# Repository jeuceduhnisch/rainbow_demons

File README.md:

# Rainbow Demons

Rainbow Demons is an independently designed Daisy Patch SM Eurorack
buffer-manipulation instrument.

## Releases

- The repository root preserves the original tested working build from
  2026-08-11, including its firmware, documentation and fabrication files.
- `Rainbow_Demons_v2/` contains the corrected 18HP hardware revision.
- `Rainbow_Demons_v2/release/` contains firmware and documentation v2.0.1.
- `Rainbow_Demons_v2/Rainbow_Demons_v2.0.1.zip` is the current complete release.
- `Rainbow_Demons_v2/Rainbow_Demons_v2.0.0.zip` remains the immutable rollback
  package.

## Version 2.0.1

Version 2 adds:

- Clock-toggle recording in Slice and Scatter: start, stop/play, start fresh.
- A Mode 2 Feedback density control that creates increasingly frequent and
  shorter randomized recording windows clockwise.
- Physical Record and REC CV priority over Mode 2 automation.
- Automatic four-second Slice and eight-second Scatter capture limits.
- A hardware-tested audio block-size correction that moves the callback cadence
  from an audible 3 kHz to 24 kHz and removes the high-pitched harmonic comb.

The v2.0.1 firmware was built, flashed, and tested on the target module on
2026-09-29. Tape, Slice, Scatter, recording, playback, three-head operation,
controls and mode switching passed without reported crackling or dropouts.

## Independent-design disclaimer

Rainbow Demons is inspired by broad buffer-manipulation ideas associated with
MTL ASM's Count to 5. It is not a clone, reproduction, port, or claim of exact
pedal behavior. No original source code, firmware, schematics, PCB files, or
proprietary design material were used. This project is not affiliated with or
endorsed by MTL ASM.

## License

This project is released under the Unlicense. See [LICENSE](LICENSE).

## Acknowledgments

Documentation, cleanup, and release organization were assisted by OpenAI Codex.

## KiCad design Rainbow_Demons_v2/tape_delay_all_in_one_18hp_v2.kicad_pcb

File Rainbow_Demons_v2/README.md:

# Rainbow Demons v2

## Tape Delay 18HP All-In-One PCB and Faceplate

This revision corrects the Alpha RD901F potentiometer and QingPu WQP-PJ398SM / Thonkiconn footprints, fixes the rear-mounted Daisy Patch SM pin mirroring, and removes the carrier PCB material behind the top and bottom Eurorack rails. The separate faceplate remains the full 128.5 mm Eurorack height.

Electrical notes:

- 10-pin Eurorack power is routed as pins 1-2 `-12V`, pins 3-8 `GND`, pins 9-10 `+12V`.
- The Patch SM `3V3` output on A10 feeds the five potentiometer high-side pins.
- The Patch SM `5V` output is not used by this tape-delay control board.
- Potentiometers are wired as `GND / wiper signal / 3V3`.
- Pot electrical pads are on 2.50 mm centers and mounting tabs are 9.60 mm apart, matching KiCad's official Alpha RD901F-40-00D footprint.
- RV2 is rotated 180 degrees behind the panel so its real Alpha-style pin row clears the Daisy Patch SM A5/A6 area.
- FREEZE and REVERSE are momentary switches to ground using the Wurth `430476085716` 12 x 12 mm THT footprint.
- Each LED has two LED holes plus two inline series-resistor holes; install a resistor between `R_SIG` and `R_LED_A`.
- The square/rectangular LED hole is cathode/ground.
- The square/rectangular jack hole is sleeve/ground.
- Jack pad centers are sleeve `-6.48 mm`, switch normal `-3.38 mm`, and tip `+4.92 mm` relative to the panel jack center.
- Each jack includes the manufacturer-recommended 3.0 mm NPTH beneath the barrel center.
- The populated carrier outline is 91.44 x 111.50 mm, spanning panel coordinates y=8.50 through y=120.00; there is no carrier material in either rail zone.
- The rear-mounted Patch SM footprint is mirrored before rotation so carrier A1 lands on module A1, A5 on A5, and all other named pins remain one-to-one.
- IN R is normalled from IN L through the jack switch contact.
- IN R is normalled from IN L. The OUT L and OUT R switch contacts are intentionally unconnected.

Fabrication status:

- The main PCB and faceplate were generated as KiCad 10 PCB files.
- KiCad CLI DRC on 2026-07-21 reported 0 violations and 0 unconnected items for both generated boards.
- Run KiCad DRC again before ordering after any manual edits.
- This layout uses generic 9 mm vertical pot, QingPu/Thonkiconn PJ398SM-style 3-pin jack, and 5 mm LED footprints. Verify against the exact parts you will buy before a full production order.

Files:

- `tape_delay_all_in_one_18hp_v2.kicad_pcb`: routed main PCB with corrected footprints, power mapping, and rail clearance.
- `tape_delay_faceplate_18hp_v2.kicad_pcb`: matching full-height FR4 faceplate.
- `faceplate_editable.svg`: editable faceplate art/text template.
- `tape_delay_all_in_one_wiring_map.csv`: Patch SM pin assignments.
- `main_gerbers.zip`: main PCB fabrication package, after export.
- `faceplate_gerbers.zip`: faceplate fabrication package, after export.

## Firmware and build release 2.0.1

The complete clock-toggle and random-density firmware release is in
`release/`. It includes source, flashable binary, BOM, build guide, PCB
modifications, quick start and the six-page combined manual.

The packaged current release is `Rainbow_Demons_v2.0.1.zip`; the unchanged
`Rainbow_Demons_v2.0.0.zip` is retained for rollback. Version 2 adds clock-edge
start/stop recording in Slice and Scatter plus randomized Mode 2 recording
density on the Feedback control. Version 2.0.1 changes only the audio block
size from 16 to 2, moving the callback cadence from 3 kHz to 24 kHz. The new
firmware built, flashed and passed the complete hands-on mode test on
2026-09-29 without reported crackling or dropouts.

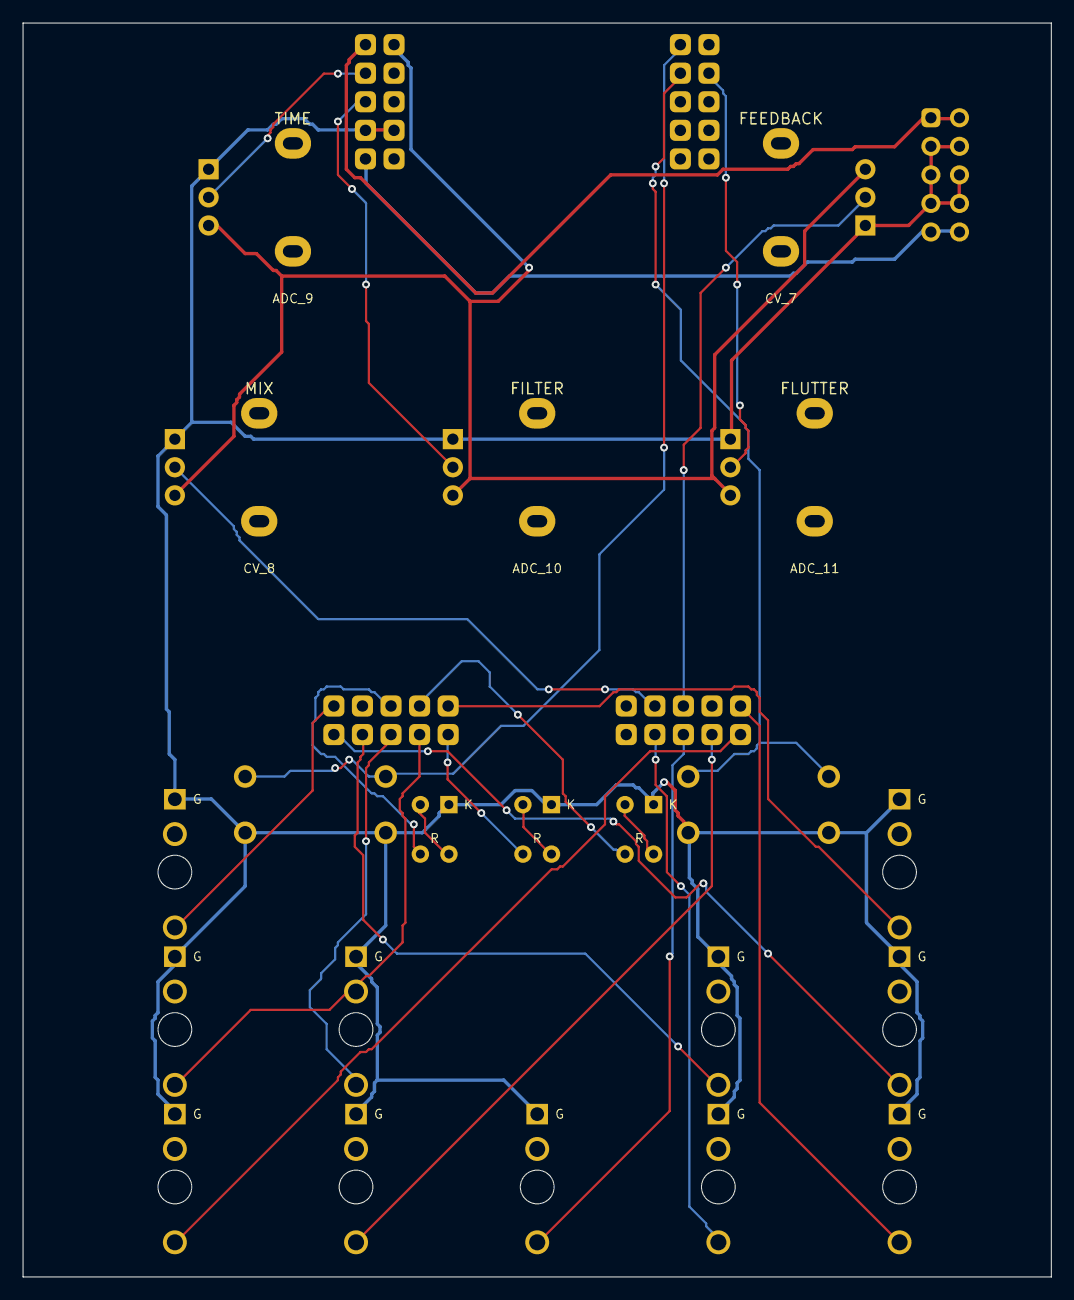
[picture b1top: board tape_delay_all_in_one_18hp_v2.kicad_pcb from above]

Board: 2 copper layers, 91.4 x 111.5 mm, 34 parts (0 on the bottom side), 28 nets.

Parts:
D1: TEMPO; LED_5mm_With_Series_Resistor_Pads
D2: FREEZE; LED_5mm_With_Series_Resistor_Pads
D3: REV; LED_5mm_With_Series_Resistor_Pads
J1: CLK IN; Jack_3.5mm_QingPu_WQP-PJ398SM_ShaftOrigin
J1_BARREL, J2_BARREL, J3_BARREL, J4_BARREL, J5_BARREL, J6_BARREL, J7_BARREL, J8_BARREL, J9_BARREL, J10_BARREL, J11_BARREL: NPTH 3mm; NPTH_3mm
J2: CLK OUT; Jack_3.5mm_QingPu_WQP-PJ398SM_ShaftOrigin
J3: IN L; Jack_3.5mm_QingPu_WQP-PJ398SM_ShaftOrigin
J4: IN R; Jack_3.5mm_QingPu_WQP-PJ398SM_ShaftOrigin
J5: OUT L; Jack_3.5mm_QingPu_WQP-PJ398SM_ShaftOrigin
J6: OUT R; Jack_3.5mm_QingPu_WQP-PJ398SM_ShaftOrigin
J7: TIME; Jack_3.5mm_QingPu_WQP-PJ398SM_ShaftOrigin
J8: FEEDBACK; Jack_3.5mm_QingPu_WQP-PJ398SM_ShaftOrigin
J9: MIX; Jack_3.5mm_QingPu_WQP-PJ398SM_ShaftOrigin
J10: FILTER; Jack_3.5mm_QingPu_WQP-PJ398SM_ShaftOrigin
J11: FLUTTER; Jack_3.5mm_QingPu_WQP-PJ398SM_ShaftOrigin
J_PWR: 10 pin Eurorack power; EURORACK_10PIN_POWER_REAR
M1: Daisy Patch SM; Daisy_Patch_SM_PTH_Rear
RV1: TIME; Alpha_RD901F_9mm_Vertical_Pot_ShaftOrigin
RV2: FEEDBACK; Alpha_RD901F_9mm_Vertical_Pot_ShaftOrigin
RV3: MIX; Alpha_RD901F_9mm_Vertical_Pot_ShaftOrigin
RV4: FILTER; Alpha_RD901F_9mm_Vertical_Pot_ShaftOrigin
RV5: FLUTTER; Alpha_RD901F_9mm_Vertical_Pot_ShaftOrigin
SW1, SW2: Wurth 430476085716; Wurth_WS-TATV_430476085716_12x12_THT

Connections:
ADC_9: M1.A2, RV1.2_SIG
ADC_10: M1.A3, RV4.2_SIG
ADC_11: M1.D9, RV5.2_SIG
AUDIO_IN_LEFT: J3.TIP_SIG, J4.SW, M1.B4
AUDIO_IN_RIGHT: J4.TIP_SIG, M1.B3
AUDIO_OUT_LEFT: J5.TIP_SIG, M1.B2
AUDIO_OUT_RIGHT: J6.TIP_SIG, M1.B1
CV_1: J7.TIP_SIG, M1.C5
CV_2: J8.TIP_SIG, M1.C4
CV_3: J9.TIP_SIG, M1.C3
CV_4: J10.TIP_SIG, M1.C2
CV_5: J11.TIP_SIG, M1.C6
CV_7: M1.C8, RV2.2_SIG
CV_8: M1.C9, RV3.2_SIG
FREEZE_BTN: M1.D1, SW1.1_SIG, SW1.2_SIG
GATE_IN_1: J1.TIP_SIG, M1.B10
GATE_OUT_2: J2.TIP_SIG, M1.B6
GND: D1.K_GND, D2.K_GND, D3.K_GND, J1.SLEEVE_GND, J2.SLEEVE_GND, J3.SLEEVE_GND, J4.SLEEVE_GND, J5.SLEEVE_GND, J6.SLEEVE_GND, J7.SLEEVE_GND, J8.SLEEVE_GND, J9.SLEEVE_GND, J10.SLEEVE_GND, J11.SLEEVE_GND, J_PWR.3, J_PWR.4, J_PWR.5, J_PWR.6, J_PWR.7, J_PWR.8, M1.A4, M1.A7, RV1.1_GND, RV2.1_GND, RV3.1_GND, RV4.1_GND, RV5.1_GND, SW1.3_GND, SW1.4_GND, SW2.3_GND, SW2.4_GND
LED_FREEZE: D2.R_SIG, M1.B5
LED_FREEZE_A: D2.A, D2.R_LED_A
LED_REVERSE: D3.R_SIG, M1.B7
LED_REVERSE_A: D3.A, D3.R_LED_A
LED_TEMPO: D1.R_SIG, M1.B8
LED_TEMPO_A: D1.A, D1.R_LED_A
PWR_3V3: M1.A10, RV1.3_3V3, RV2.3_3V3, RV3.3_3V3, RV4.3_3V3, RV5.3_3V3
PWR_+12V: J_PWR.9, J_PWR.10, M1.A5
PWR_-12V: J_PWR.1, J_PWR.2, M1.A1
REVERSE_BTN: M1.D2, SW2.1_SIG, SW2.2_SIG

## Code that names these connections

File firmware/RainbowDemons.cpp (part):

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    // Preserve the already-built carrier wiring exactly:
    // TIME/ADC_9, FILTER/ADC_10, FLUTTER/ADC_11,
    // FEEDBACK/CV_7 and MIX/CV_8. The five panel CV inputs remain CV_1..CV_5.
    const float time_p = Clamp(patch.GetAdcValue(ADC_9), 0.0f, 1.0f);
    const float q_p    = Clamp(patch.GetAdcValue(ADC_10), 0.0f, 1.0f);
    const float len_p  = Clamp(patch.GetAdcValue(ADC_11), 0.0f, 1.0f);
    const float fb_p   = Clamp(patch.GetAdcValue(CV_7), 0.0f, 1.0f);
    const float mix_p  = CalibrateMixPot(patch.GetAdcValue(CV_8));

    const float cv1 = Clamp(patch.GetAdcValue(CV_1), -1.0f, 1.0f);
    const float cv2 = Clamp(patch.GetAdcValue(CV_2), -1.0f, 1.0f);
    const float cv3 = Clamp(patch.GetAdcValue(CV_3), -1.0f, 1.0f);
    const float cv4 = Clamp(patch.GetAdcValue(CV_4), -1.0f, 1.0f);
    // CV_5 is the jack physically located under FLUTTER on this reused board,
    // not a normalled MIX CV. Do not let its unpatched offset prevent the Mix
    // pot from reaching either endpoint.
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    if(c.mode != current_mode) OnModeChanged(c.mode);

    const bool record_pressed = record_button.Pressed();
    const bool record_trigger = patch.gate_in_1.Trig();
    if(c.mode != Mode::Tape)
    {
        if(record_pressed && !previous_record_pressed) BeginCapture(false);
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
